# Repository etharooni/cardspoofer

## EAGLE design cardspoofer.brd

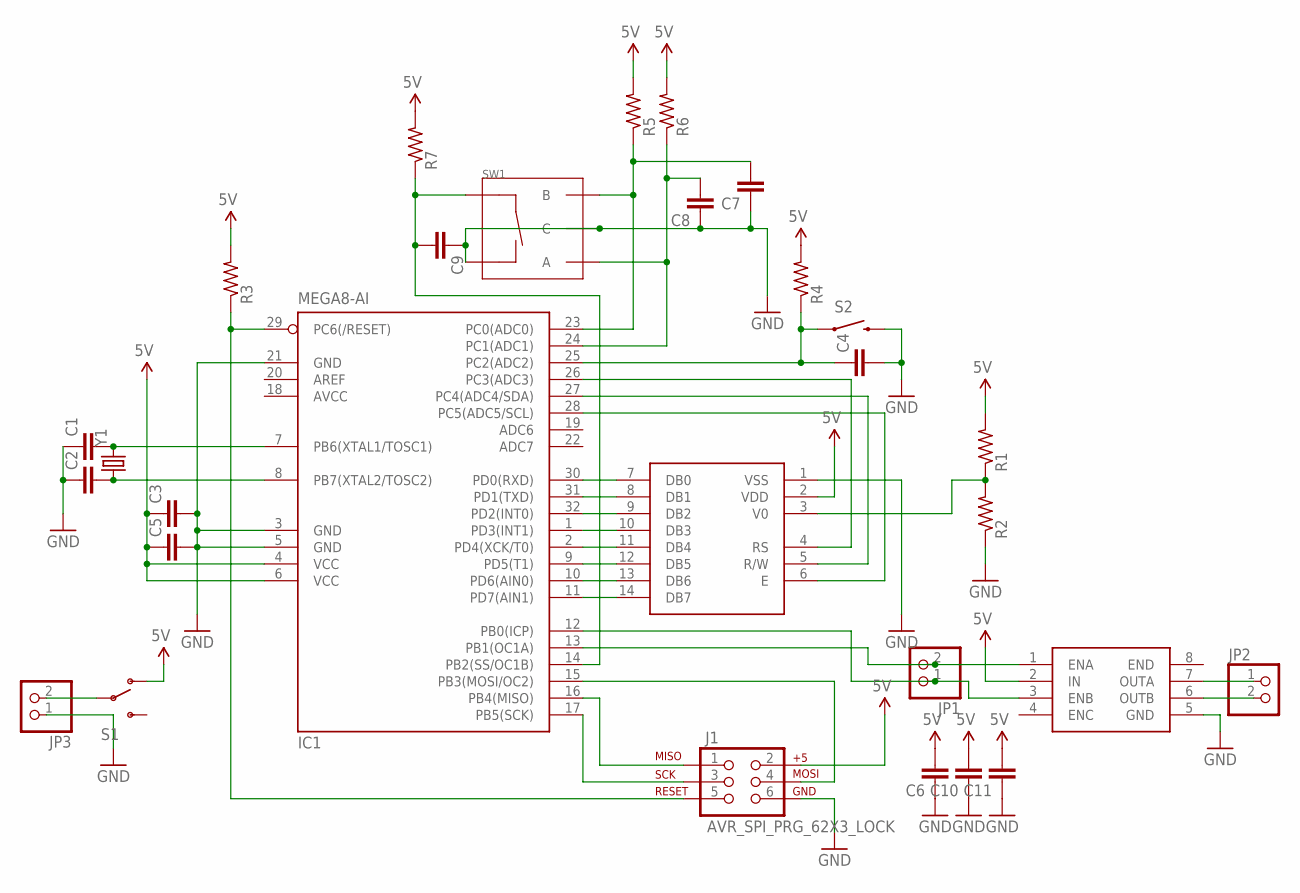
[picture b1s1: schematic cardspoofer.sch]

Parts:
C1, C2, C3, C4, C5, C6, C7, C8, C9, C10, C11: C-EUC0805K; C0805K
IC1: MEGA8-AI; TQFP32-08
J1: AVR_SPI_PRG_62X3_LOCK; 2X3_LOCK
JP1, JP2, JP3: PINHD-1X2; 1X02
R1, R2, R3, R4, R5, R6, R7: R-US_R0805; R0805
S1: SWITCH-SPDTSMD; AYZ0202
S2: SWITCH-MOMENTARY-2-SMD-1101NE; TACTILE-SWITCH-1101NE
SW1: ROTARTY_ENCODER; ROTARY_ENC_PLAIN
U$1: LCD; NHD-0208AZ-RN-YBW-ND
U$2: HBRIDGE; H-BRIDGE
Y1: CRYSTAL5X3; CRYSTAL-SMD-5X3

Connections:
5V: C3.1, C5.1, C6.2, C10.2, C11.2, IC1.4 (VCC), IC1.6 (VCC), J1.2, R1.2, R3.2, R4.2, R5.2, R6.2, R7.2, S1.1 (O), U$1.2 (VDD), U$2.2 (IN)
AVCC: IC1.18 (AVCC)
GND: C1.1, C2.1, C3.2, C4.2, C5.2, C6.1, C7.1, C8.1, C9.1, C10.1, C11.1, IC1.3 (GND), IC1.5 (GND), IC1.21 (GND), J1.6, JP3.1, R2.1, S2.2, SW1.C, SW1.SW-, U$1.1 (VSS), U$2.5 (GND)
unnamed: R1.1, R2.2, U$1.3 (V0)
unnamed: IC1.30 (PD0(RXD)), U$1.7 (DB0)
unnamed: IC1.31 (PD1(TXD)), U$1.8 (DB1)
unnamed: IC1.32 (PD2(INT0)), U$1.9 (DB2)
unnamed: IC1.1 (PD3(INT1)), U$1.10 (DB3)
unnamed: IC1.2 (PD4(XCK/T0)), U$1.11 (DB4)
unnamed: IC1.9 (PD5(T1)), U$1.12 (DB5)
unnamed: IC1.10 (PD6(AIN0)), U$1.13 (DB6)
unnamed: IC1.11 (PD7(AIN1)), U$1.14 (DB7)
unnamed: IC1.26 (PC3(ADC3)), U$1.4 (RS)
unnamed: IC1.27 (PC4(ADC4/SDA)), U$1.5 (R/W)
unnamed: IC1.28 (PC5(ADC5/SCL)), U$1.6 (E)
unnamed: IC1.29 (PC6(/RESET)), J1.5, R3.1
unnamed: IC1.17 (PB5(SCK)), J1.3
unnamed: IC1.16 (PB4(MISO)), J1.1
unnamed: IC1.15 (PB3(MOSI/OC2)), J1.4
unnamed: C1.2, IC1.7 (PB6(XTAL1/TOSC1)), Y1.3 (2)
unnamed: C2.2, IC1.8 (PB7(XTAL2/TOSC2)), Y1.1
unnamed: C4.1, IC1.25 (PC2(ADC2)), R4.1, S2.1
unnamed: IC1.13 (PB1(OC1A)), JP1.2, U$2.1 (ENA)
unnamed: IC1.12 (PB0(ICP)), JP1.1, U$2.3 (ENB)
unnamed: JP2.1, U$2.7 (OUTA)
unnamed: JP2.2, U$2.6 (OUTB)
unnamed: C7.2, IC1.23 (PC0(ADC0)), R5.1, SW1.B
unnamed: C8.2, IC1.24 (PC1(ADC1)), R6.1, SW1.A
unnamed: C9.2, IC1.14 (PB2(SS/OC1B)), R7.1, SW1.SW+
unnamed: JP3.2, S1.2

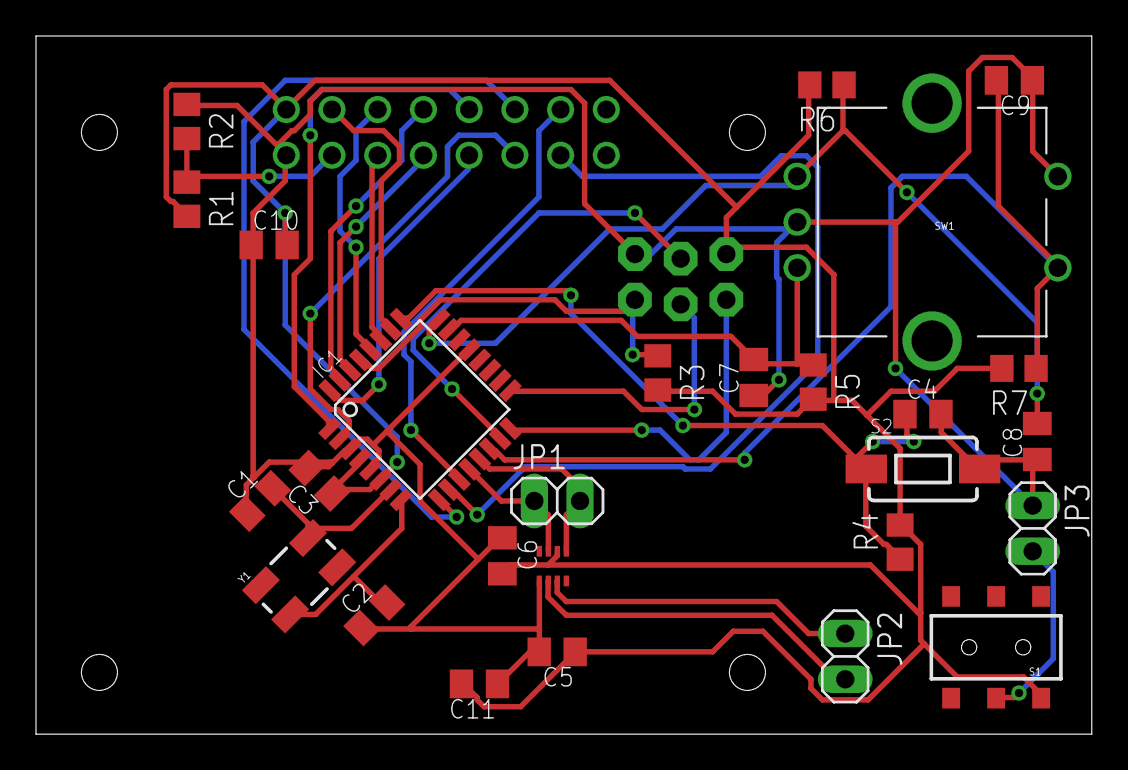
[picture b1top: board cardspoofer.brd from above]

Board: 2 copper layers, 58.7 x 38.8 mm, 29 parts (1 on the bottom side), 29 nets.

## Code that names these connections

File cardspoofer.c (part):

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//#include <avr/eeprom.h> //TODO
//#include <avr/sleep.h> //TODO

#define enc_pina 1 //PC1/PCINT8
#define enc_pinb 0 //PC0/PCINT9
#define encButtonPin 2 //PB2
#define coil_pina 0 //PB0
#define coil_pinb 1 //PB1
#define en_pin 5 //PB5
#define lcd_rsPin 3 //PC3
#define lcd_rwPin 4 //PC4
#define lcd_ePin 5 //PC5

int clockSpeed = 500;
int clockHalf = 0;
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	DDRC = 0b111000;
	PORTB &= ~(1<<en_pin); //disable drivers
	
	PCMSK1 |= (1 << PCINT8)|(1 << PCINT9)|(1 << PCINT10); //set interrupts on PCINT8 (PC0) and PCINT9 (PC1) for encoder on channel 1, and PCINT10(PC2) for button	
	PCICR |= (1 << PCIE1);//Enable channel 1 (PCINTs 8 and 9)
	sei();
	/*
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
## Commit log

2017-05-21 added duplicate card functionality
2017-05-21 three leading zeroes. oops

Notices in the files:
parts and their libraries:
SparkFun-Connectors: Licensing: Creative Commons ShareAlike 4.0 International - https://creativecommons.org/licenses/by-sa/4.0
